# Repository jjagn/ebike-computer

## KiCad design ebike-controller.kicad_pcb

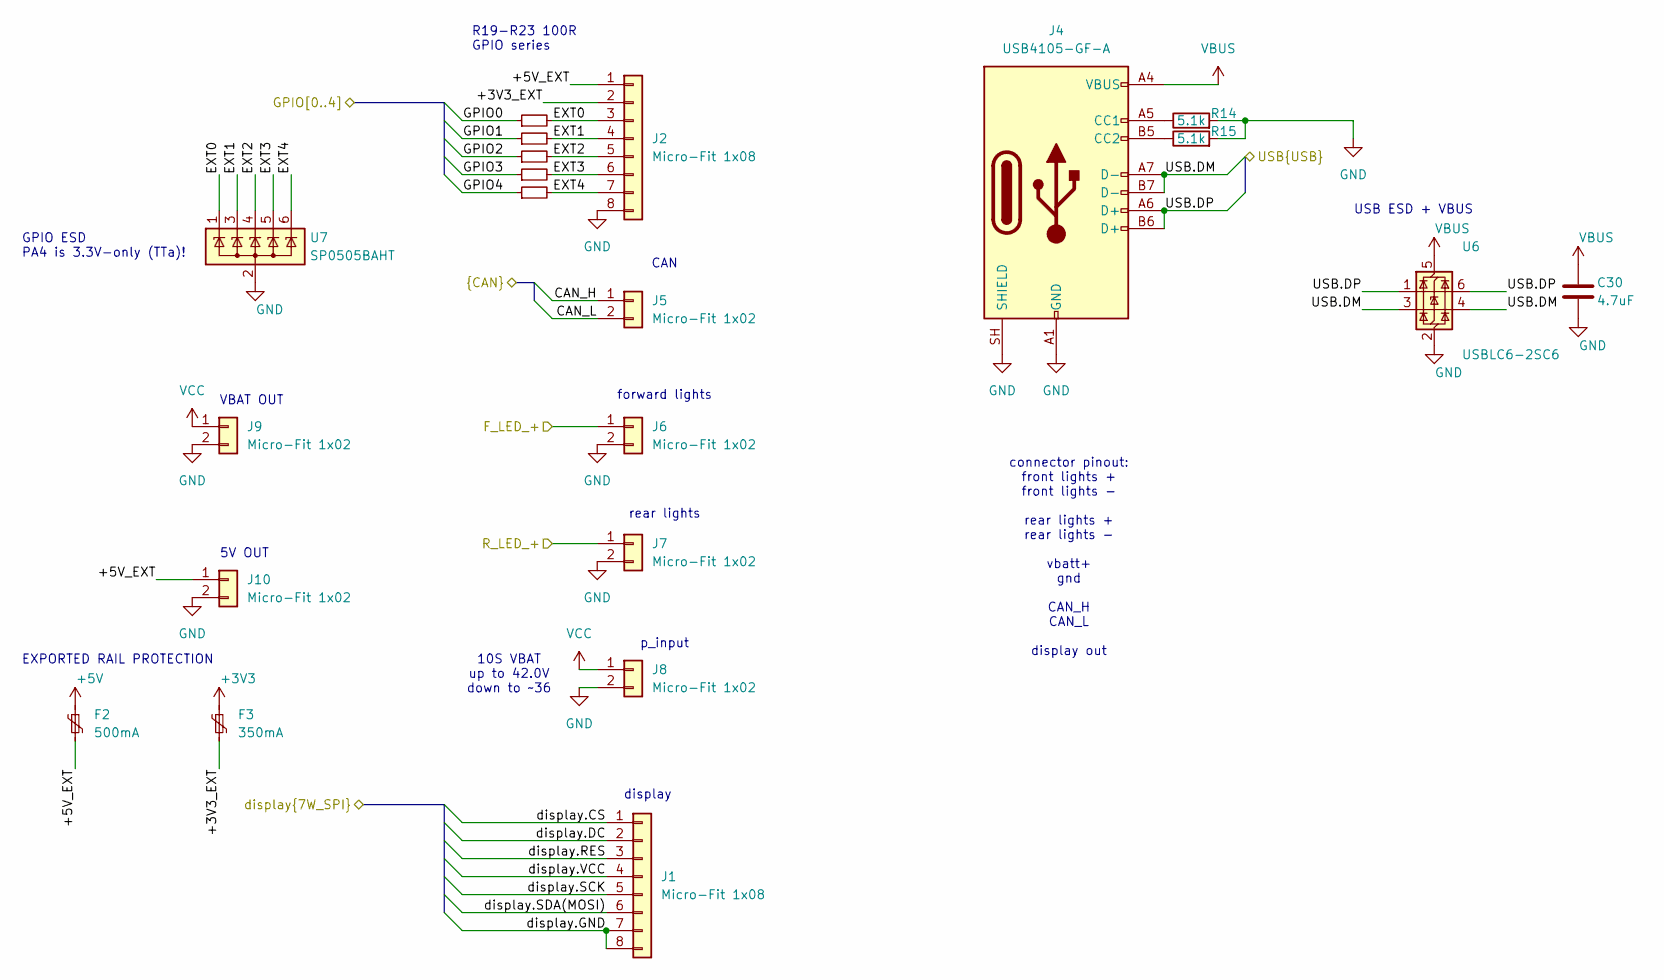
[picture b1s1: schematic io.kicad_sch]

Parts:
C30: 4.7uF; C_0603_1608Metric; Manufacturer Part Number CL10A475KO8NNNC; LCSC Part Number C19666
F2: 500mA; Fuse_0805_2012Metric; Manufacturer Part Number SMD0805B050TF; LCSC Part Number C269104
F3: 350mA; Fuse_0805_2012Metric; Manufacturer Part Number BSMD0805-035-6V; LCSC Part Number C883106
J1, J2: Micro-Fit 1x08; Molex_Micro-Fit_3.0_43650-0800_1x08_P3.00mm_Horizontal; Manufacturer Part Number 0436500800
J4: USB4105-GF-A; USB_C_Receptacle_GCT_USB4105-xx-A_16P_TopMnt_Horizontal; Manufacturer Part Number USB4105-GF-A; LCSC Part Number C3020560
J5, J6, J7, J8, J9, J10: Micro-Fit 1x02; Molex_Micro-Fit_3.0_43650-0200_1x02_P3.00mm_Horizontal; Manufacturer Part Number 0436500200
R14, R15: 5.1k; R_0402_1005Metric; Manufacturer Part Number 0402WGF5101TCE; LCSC Part Number C25905
R19, R20, R21, R22, R23: 100R; R_0402_1005Metric; Manufacturer Part Number 0402WGF1000TCE; LCSC Part Number C25076
U6: USBLC6-2SC6; SOT-23-6; Manufacturer Part Number USBLC6-2SC6; LCSC Part Number C7519
U7: SP0505BAHT; SOT-23-6; Manufacturer Part Number SP0505BAHTG; LCSC Part Number C151299

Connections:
+3V3: F3.1, J1.4; also elsewhere on the board
+5V: F2.1; also elsewhere on the board
/IO/+3V3_EXT: F3.2, J2.2
/IO/+5V_EXT: F2.2, J2.1, J10.1
/IO/CAN_H: J5.1; also elsewhere on the board
/IO/CAN_L: J5.2; also elsewhere on the board
/IO/EXT0: J2.3, R19.2, U7.1 (K)
/IO/EXT1: J2.4, R20.2, U7.3 (K)
/IO/EXT2: J2.5, R21.2, U7.4 (K)
/IO/EXT3: J2.6, R22.2, U7.5 (K)
/IO/EXT4: J2.7, R23.2, U7.6 (K)
/IO/F_LED_+: J6.1
/IO/GPIO0: R19.1; also elsewhere on the board
/IO/GPIO1: R20.1; also elsewhere on the board
/IO/GPIO2: R21.1; also elsewhere on the board
/IO/GPIO3: R22.1; also elsewhere on the board
/IO/GPIO4: R23.1; also elsewhere on the board
/IO/R_LED_+: J7.1
/IO/USB.DM: J4.A7 (D-), J4.B7 (D-), U6.3 (I/O2), U6.4 (I/O2); also elsewhere on the board
/IO/USB.DP: J4.A6 (D+), J4.B6 (D+), U6.1 (I/O1), U6.6 (I/O1); also elsewhere on the board
/IO/display.CS: J1.1; also elsewhere on the board
/IO/display.DC: J1.2; also elsewhere on the board
/IO/display.RES: J1.3; also elsewhere on the board
/IO/display.SCK: J1.5; also elsewhere on the board
/IO/display.SDA(MOSI): J1.6; also elsewhere on the board
GND: C30.2, J1.7, J1.8, J2.8, J4.A1 (GND), J4.A12 (GND), J4.B1 (GND), J4.B12 (GND), J4.SH (SHIELD), J6.2, J7.2, J8.2, J9.2, J10.2, R14.2, R15.2, U6.2 (GND), U7.2 (A); also elsewhere on the board
unnamed: J4.A5 (CC1), R14.1
unnamed: J4.B5 (CC2), R15.1
VBUS: C30.1, J4.A4 (VBUS), J4.A9 (VBUS), J4.B4 (VBUS), J4.B9 (VBUS), U6.5 (VBUS); also elsewhere on the board
VCC: J8.1, J9.1; also elsewhere on the board

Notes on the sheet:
connector pinout: front lights + front lights - rear lights + rear lights - vbatt+ gnd CAN_H CAN_L display out
5V OUT
CAN
p_input
VBAT OUT
10S VBAT up to 42.0V down to ~36
forward lights
display
rear lights
USB ESD + VBUS
R19-R23 100R GPIO series
GPIO ESD PA4 is 3.3V-only (TTa)!
EXPORTED RAIL PROTECTION

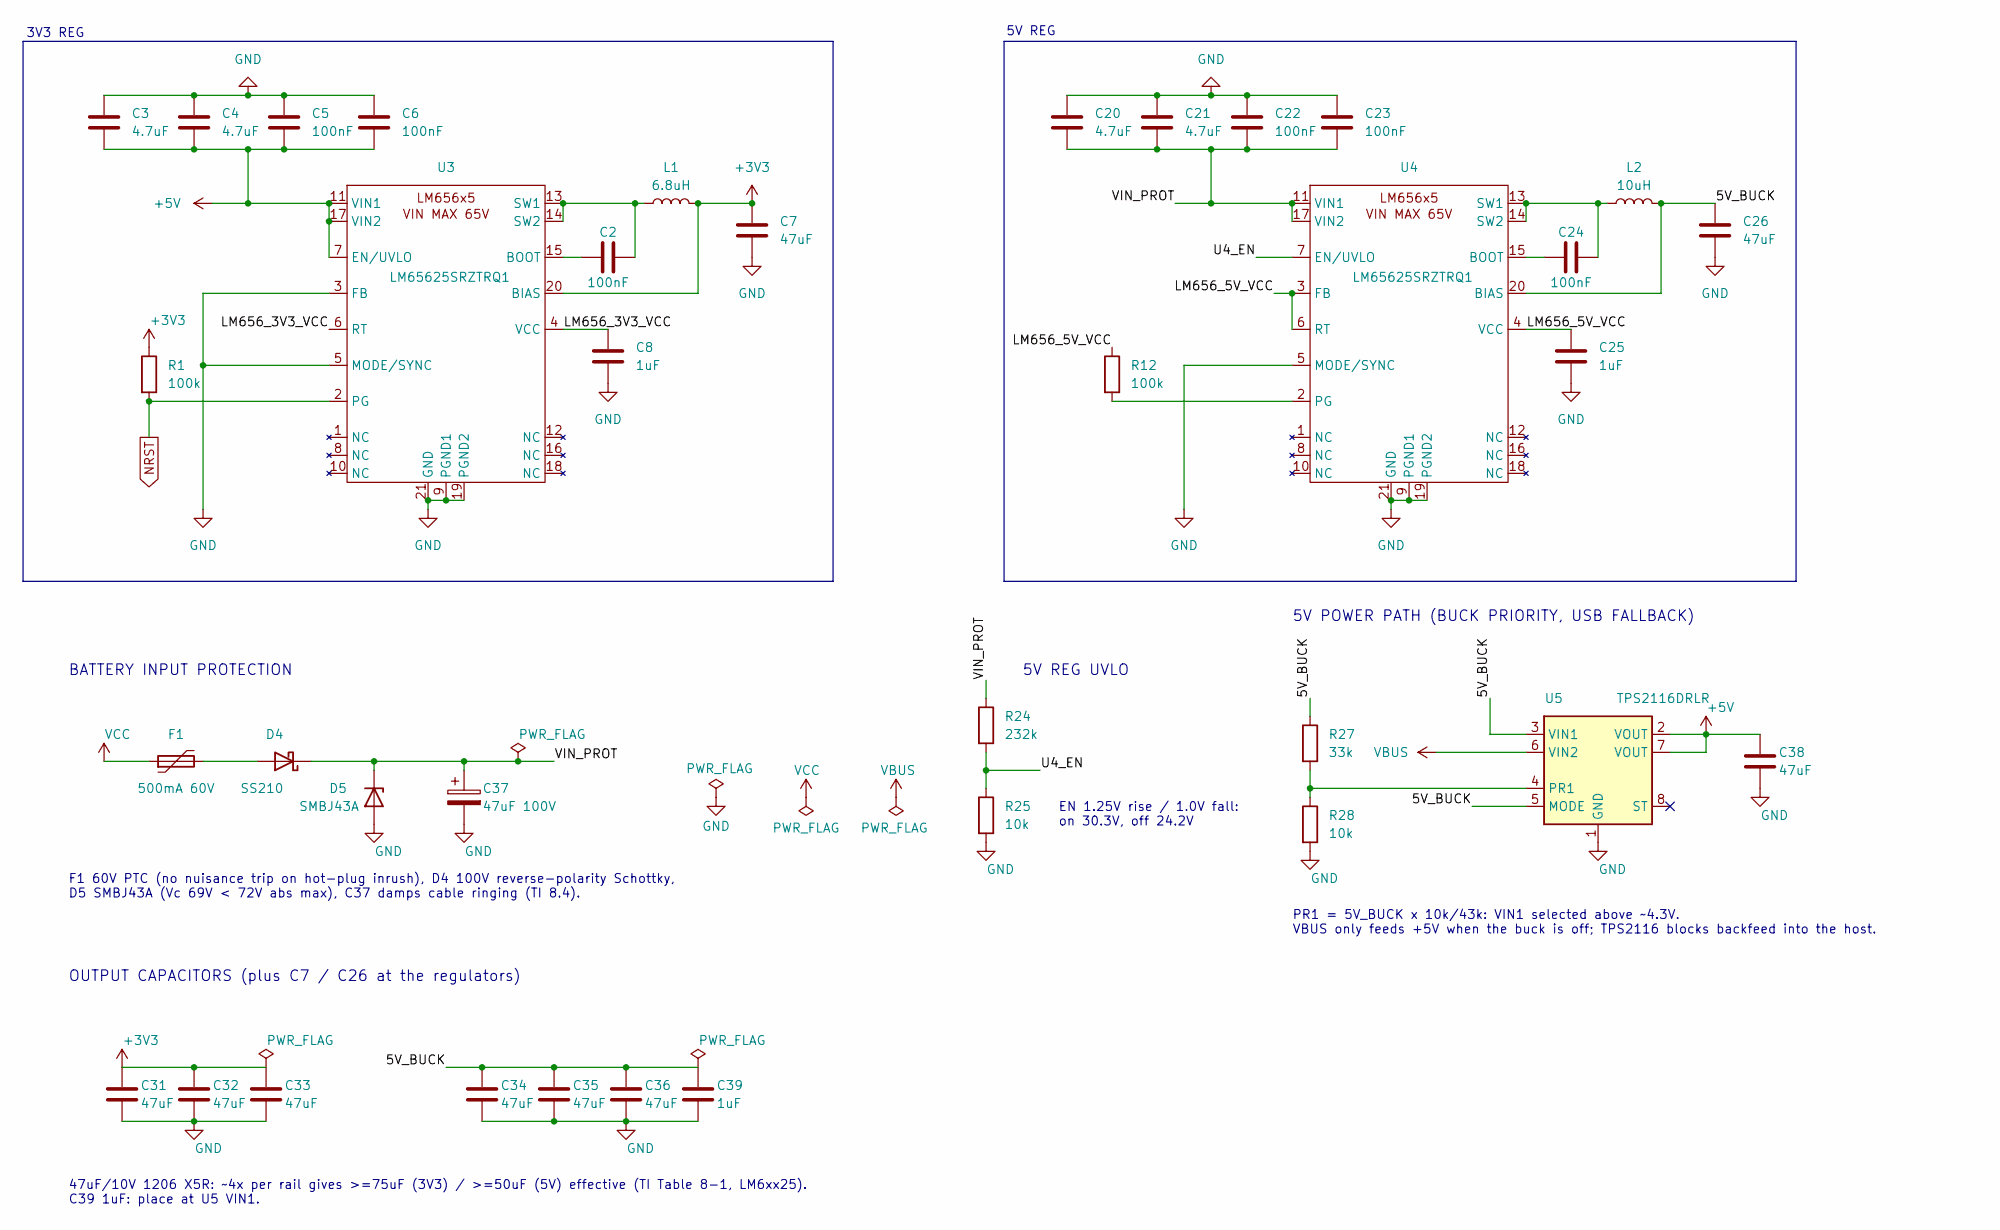
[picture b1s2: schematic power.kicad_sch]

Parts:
C2, C5, C6, C24: 100nF; C_0402_1005Metric; Manufacturer Part Number CL05B104KB54PNC; LCSC Part Number C307331
C3, C4: 4.7uF; C_0805_2012Metric; Manufacturer Part Number CL21A475KAQNNNE; LCSC Part Number C1779
C7, C26, C31, C32, C33, C34, C35, C36, C38: 47uF; C_1206_3216Metric; Manufacturer Part Number CL31A476MPHNNNE; LCSC Part Number C96123
C8, C25, C39: 1uF; C_0402_1005Metric; Manufacturer Part Number CL05A105KA5NQNC; LCSC Part Number C52923
C20, C21: 4.7uF; C_1210_3225Metric; Manufacturer Part Number CL32Y475KCIVPNE; LCSC Part Number C2803397
C22, C23: 100nF; C_0603_1608Metric; Manufacturer Part Number CL10B104KC8NNNC; LCSC Part Number C15725
C37: 47uF 100V; CP_Elec_10x10; Manufacturer Part Number VEJ470M2ATR-1010; LCSC Part Number C134777
D4: SS210; D_SMA; Manufacturer Part Number SS210; LCSC Part Number C14996
D5: SMBJ43A; D_SMB; Manufacturer Part Number SMBJ43A; LCSC Part Number C5353274
F1: 500mA 60V; Fuse_1812_4532Metric; Manufacturer Part Number mSMD050-60V; LCSC Part Number C70113
L1: 6.8uH; Inductor_SMD_7.4mmx6.6mm; Manufacturer Part Number GSM0630-6R8-M; LCSC Part Number C51933839
L2: 10uH; Inductor_SMD_7.4mmx6.6mm; Manufacturer Part Number SRG0630-100-M; LCSC Part Number C53462991
R1, R12: 100k; R_0402_1005Metric; Manufacturer Part Number 0402WGF1003TCE; LCSC Part Number C25741
R24: 232k; R_0402_1005Metric; Manufacturer Part Number FRC0402F2323TS; LCSC Part Number C3013159
R25, R28: 10k; R_0402_1005Metric; Manufacturer Part Number 0402WGF1002TCE; LCSC Part Number C25744
R27: 33k; R_0402_1005Metric; Manufacturer Part Number 0402WGF3302TCE; LCSC Part Number C25779
U3, U4: LM65625SRZTRQ1; TI_RZT0020A; Manufacturer Part Number LM65625SRZTRQ1; LCSC Part Number C49305977
U5: TPS2116DRLR; SOT-583-8; Manufacturer Part Number TPS2116DRLR; LCSC Part Number C3235557

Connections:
+3V3: C7.1, C31.1, C32.1, C33.1, L1.2, R1.1, U3.20 (BIAS); also elsewhere on the board
+5V: C3.2, C4.2, C5.2, C6.2, C38.1, U3.7 (EN/UVLO), U3.11 (VIN1), U3.17 (VIN2), U5.2 (VOUT), U5.7 (VOUT); also elsewhere on the board
/Power/5V_BUCK: C26.1, C34.1, C35.1, C36.1, C39.1, L2.2, R27.1, U4.20 (BIAS), U5.3 (VIN1), U5.5 (MODE)
/Power/LM656_3V3_VCC: C8.1, U3.4 (VCC), U3.6 (RT)
/Power/LM656_5V_VCC: C25.1, R12.1, U4.3 (FB), U4.4 (VCC), U4.6 (RT)
/Power/U4_EN: R24.2, R25.1, U4.7 (EN/UVLO)
/Power/VIN_PROT: C20.2, C21.2, C22.2, C23.2, C37.1, D4.1 (K), D5.1 (K), R24.1, U4.11 (VIN1), U4.17 (VIN2)
GND: C3.1, C4.1, C5.1, C6.1, C7.2, C8.2, C20.1, C21.1, C22.1, C23.1, C25.2, C26.2, C31.2, C32.2, C33.2, C34.2, C35.2, C36.2, C37.2, C38.2, C39.2, D5.2 (A), R25.2, R28.2, U3.3 (FB), U3.5 (MODE/SYNC), U3.9 (PGND1), U3.19 (PGND2), U3.21 (GND), U4.5 (MODE/SYNC), U4.9 (PGND1), U4.19 (PGND2), U4.21 (GND), U5.1 (GND); also elsewhere on the board
NRST: R1.2, U3.2 (PG); also elsewhere on the board
unnamed: D4.2 (A), F1.2
unnamed: C2.1, U3.15 (BOOT)
unnamed: C2.2, L1.1, U3.13 (SW1), U3.14 (SW2)
unnamed: C24.1, U4.15 (BOOT)
unnamed: R12.2, U4.2 (PG)
unnamed: C24.2, L2.1, U4.13 (SW1), U4.14 (SW2)
unnamed: R27.2, R28.1, U5.4 (PR1)
VBUS: U5.6 (VIN2); also elsewhere on the board
VCC: F1.1; also elsewhere on the board

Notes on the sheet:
PR1 = 5V_BUCK x 10k/43k: VIN1 selected above ~4.3V. VBUS only feeds +5V when the buck is off; TPS2116 blocks backfeed into the host.
5V REG
47uF/10V 1206 X5R: ~4x per rail gives >=75uF (3V3) / >=50uF (5V) effective (TI Table 8-1, LM6xx25). C39 1uF: place at U5 VIN1.
BATTERY INPUT PROTECTION
EN 1.25V rise / 1.0V fall: on 30.3V, off 24.2V
5V REG UVLO
5V POWER PATH (BUCK PRIORITY, USB FALLBACK)
OUTPUT CAPACITORS (plus C7 / C26 at the regulators)
3V3 REG
F1 60V PTC (no nuisance trip on hot-plug inrush), D4 100V reverse-polarity Schottky, D5 SMBJ43A (Vc 69V < 72V abs max), C37 damps cable ringing (TI 8.4).

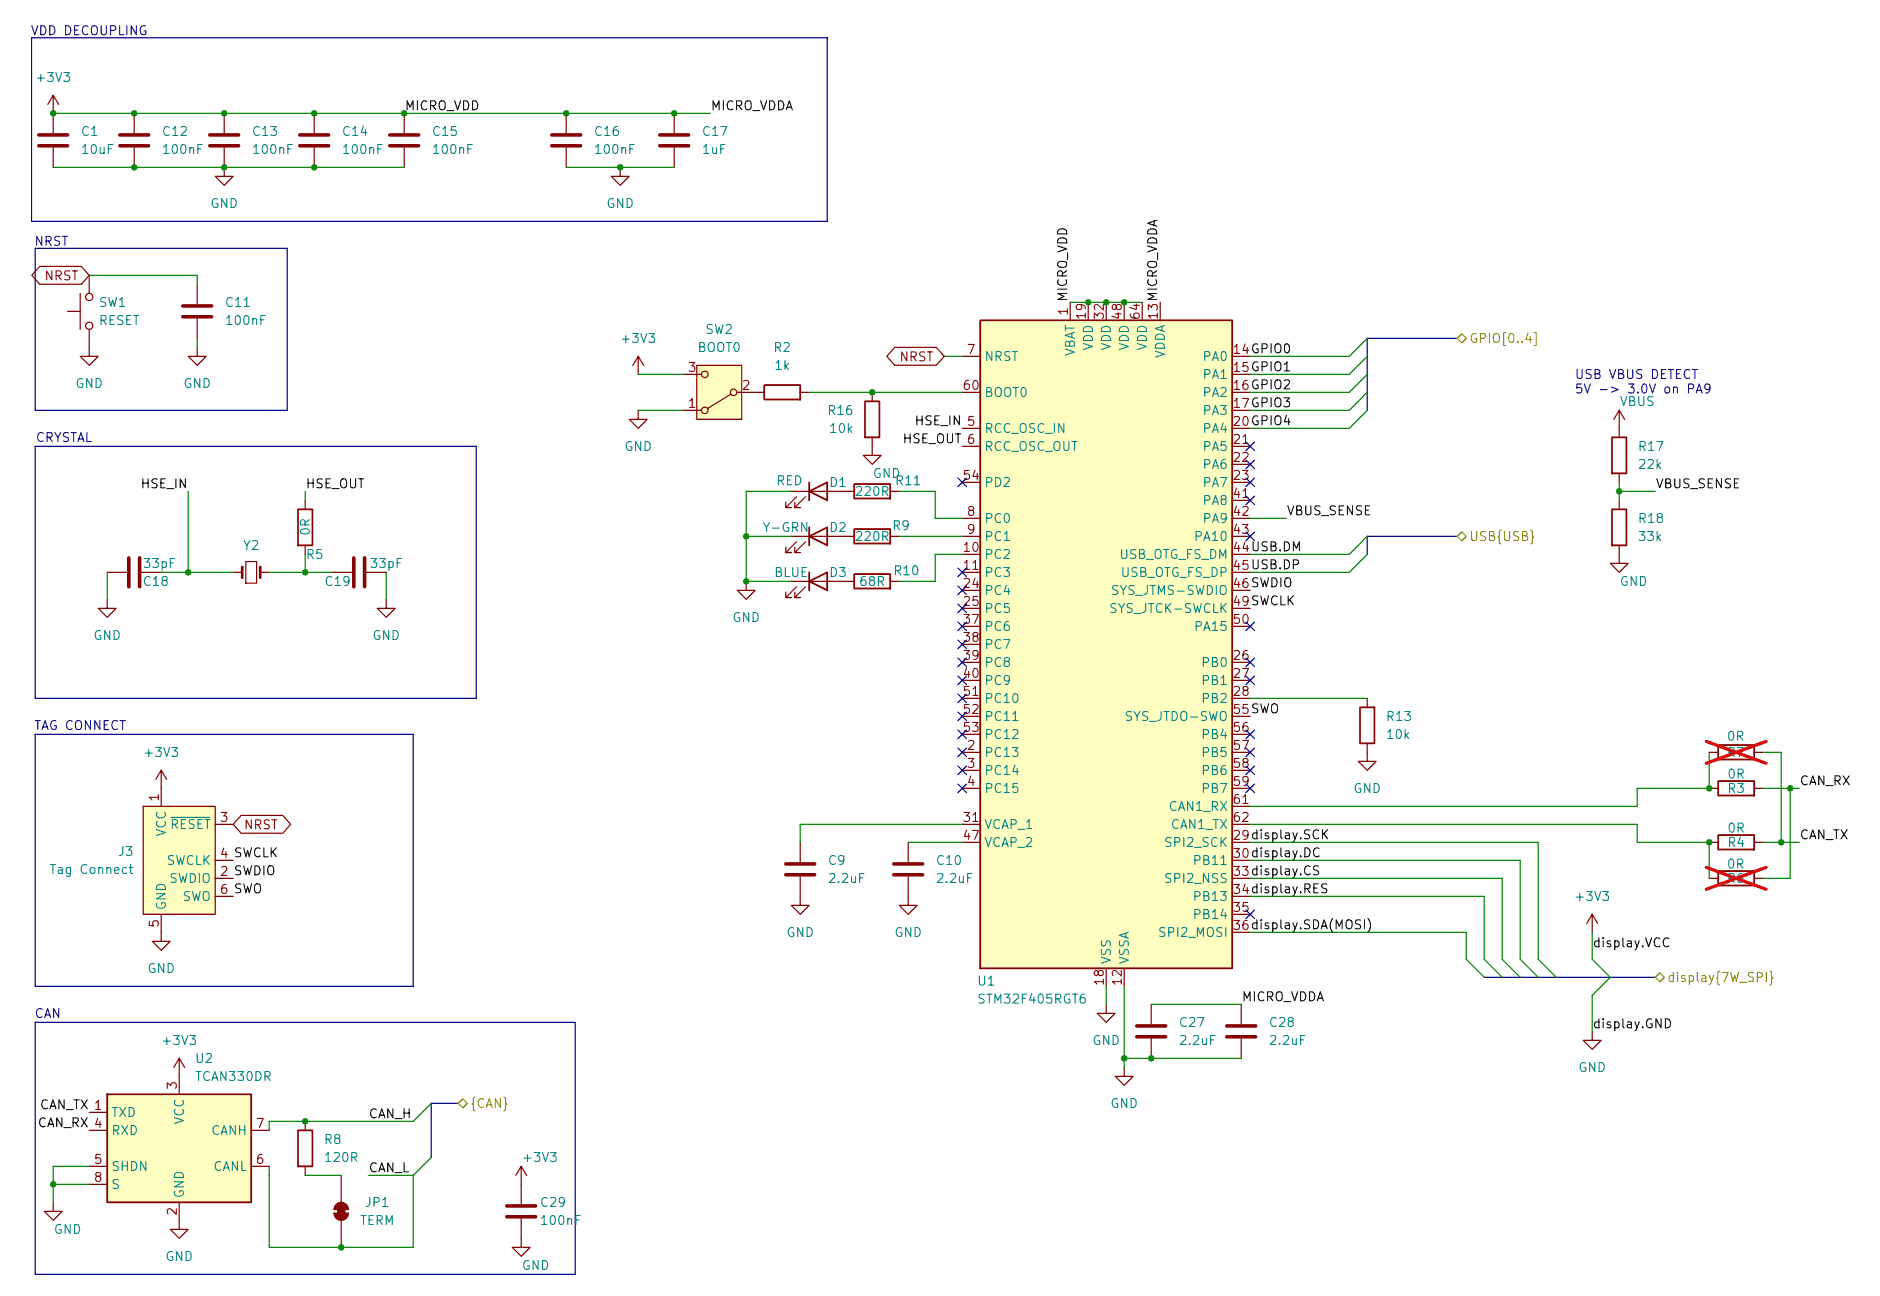
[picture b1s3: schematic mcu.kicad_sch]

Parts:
C1: 10uF; C_0805_2012Metric; Manufacturer Part Number CL21A106KAYNNNE; LCSC Part Number C15850
C9, C10, C27, C28: 2.2uF; C_0402_1005Metric; Manufacturer Part Number CL05A225MQ5NSNC; LCSC Part Number C12530
C11, C12, C13, C14, C15, C16, C29: 100nF; C_0402_1005Metric; Manufacturer Part Number CL05B104KB54PNC; LCSC Part Number C307331
C17: 1uF; C_0402_1005Metric; Manufacturer Part Number CL05A105KA5NQNC; LCSC Part Number C52923
C18, C19: 33pF; C_0402_1005Metric; Manufacturer Part Number 0402CG330J500NT; LCSC Part Number C1562
D1: RED; LED_0603_1608Metric; Manufacturer Part Number KT-0603R; LCSC Part Number C2286
D2: Y-GRN; LED_0603_1608Metric; Manufacturer Part Number KT-0603YG; LCSC Part Number C2289
D3: BLUE; LED_0603_1608Metric; Manufacturer Part Number 19-217/BHC-ZL1M2RY/6T; LCSC Part Number C2986058
J3: Tag Connect; Tag-Connect_TC2030-IDC-FP_2x03_P1.27mm_Vertical
JP1: TERM; SolderJumper-2_P1.3mm_Bridged_RoundedPad1.0x1.5mm
R2: 1k; R_0402_1005Metric; Manufacturer Part Number 0402WGF1001TCE; LCSC Part Number C11702
R3, R4, R5: 0R; R_0603_1608Metric; Manufacturer Part Number 0603WAF0000T5E; LCSC Part Number C21189
R6, R7: 0R; R_0603_1608Metric; Manufacturer Part Number 0603WAF0000T5E; LCSC Part Number C21189; not fitted
R8: 120R; R_0402_1005Metric; Manufacturer Part Number 0402WGF1200TCE; LCSC Part Number C25079
R9, R11: 220R; R_0402_1005Metric; Manufacturer Part Number 0402WGF2200TCE; LCSC Part Number C25091
R10: 68R; R_0402_1005Metric; Manufacturer Part Number FRC0402F68R0TS; LCSC Part Number C2909380
R13, R16: 10k; R_0402_1005Metric; Manufacturer Part Number 0402WGF1002TCE; LCSC Part Number C25744
R17: 22k; R_0402_1005Metric; Manufacturer Part Number 0402WGF2202TCE; LCSC Part Number C25768
R18: 33k; R_0402_1005Metric; Manufacturer Part Number 0402WGF3302TCE; LCSC Part Number C25779
SW1: RESET; SW_Push_1P1T_XKB_TS-1187A; Manufacturer Part Number TS-1187A-B-A-B; LCSC Part Number C318884
SW2: BOOT0; SW_SPDT_Shouhan_MSK12C02; Manufacturer Part Number MSK12C02; LCSC Part Number C431540
U1: STM32F405RGT6; LQFP-64_10x10mm_P0.5mm; Manufacturer Part Number STM32F405RGT6; LCSC Part Number C15742
U2: TCAN330DR; SOIC-8_3.9x4.9mm_P1.27mm; Manufacturer Part Number TCAN330DR; LCSC Part Number C2652876
Y2: 8MHz 20pF; Crystal_SMD_5032-2Pin_5.0x3.2mm; Manufacturer Part Number X50328MSB2GI; LCSC Part Number C115962

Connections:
+3V3: C1.1, C12.1, C13.1, C14.1, C15.1, C16.1, C17.1, C27.2, C28.2, C29.1, J3.1 (VCC), SW2.3 (C), U1.1 (VBAT), U1.13 (VDDA), U1.19 (VDD), U1.32 (VDD), U1.48 (VDD), U1.64 (VDD), U2.3 (VCC); also elsewhere on the board
/IO/CAN_H: R8.1, U2.7 (CANH); also elsewhere on the board
/IO/CAN_L: JP1.1 (A), U2.6 (CANL); also elsewhere on the board
/IO/GPIO0: U1.14 (PA0); also elsewhere on the board
/IO/GPIO1: U1.15 (PA1); also elsewhere on the board
/IO/GPIO2: U1.16 (PA2); also elsewhere on the board
/IO/GPIO3: U1.17 (PA3); also elsewhere on the board
/IO/GPIO4: U1.20 (PA4); also elsewhere on the board
/IO/USB.DM: U1.44 (USB_OTG_FS_DM); also elsewhere on the board
/IO/USB.DP: U1.45 (USB_OTG_FS_DP); also elsewhere on the board
/IO/display.CS: U1.33 (SPI2_NSS); also elsewhere on the board
/IO/display.DC: U1.30 (PB11); also elsewhere on the board
/IO/display.RES: U1.34 (PB13); also elsewhere on the board
/IO/display.SCK: U1.29 (SPI2_SCK); also elsewhere on the board
/IO/display.SDA(MOSI): U1.36 (SPI2_MOSI); also elsewhere on the board
/MCU/CAN_RX: R3.2, R6.1, U2.4 (RXD)
/MCU/CAN_TX: R4.2, R7.1, U2.1 (TXD)
/MCU/HSE_IN: C18.2, U1.5 (RCC_OSC_IN), Y2.1
/MCU/HSE_OUT: R5.1, U1.6 (RCC_OSC_OUT)
/MCU/SWCLK: J3.4 (SWCLK), U1.49 (SYS_JTCK-SWCLK)
/MCU/SWDIO: J3.2 (SWDIO), U1.46 (SYS_JTMS-SWDIO)
/MCU/SWO: J3.6 (SWO), U1.55 (SYS_JTDO-SWO)
/MCU/VBUS_SENSE: R17.2, R18.1, U1.42 (PA9)
GND: C1.2, C9.1, C10.1, C11.2, C12.2, C13.2, C14.2, C15.2, C16.2, C17.2, C18.1, C19.2, C27.1, C28.1, C29.2, D1.1 (K), D2.1 (K), D3.1 (K), J3.5 (GND), R13.1, R16.2, R18.2, SW1.1, SW2.1 (A), U1.12 (VSSA), U1.18 (VSS), U1.63 (VSS), U2.2 (GND), U2.5 (SHDN), U2.8 (S); also elsewhere on the board
NRST: C11.1, J3.3 (~RESET), SW1.2, U1.7 (NRST); also elsewhere on the board
unnamed: C19.1, R5.2, Y2.2
unnamed: D1.2 (A), R11.1
unnamed: D2.2 (A), R9.1
unnamed: D3.2 (A), R10.1
unnamed: JP1.2 (B), R8.2
unnamed: R2.1, SW2.2 (B)
unnamed: R2.2, R16.1, U1.60 (BOOT0)
unnamed: R13.2, U1.28 (PB2)
unnamed: R3.1, R7.2, U1.61 (CAN1_RX)
unnamed: R4.1, R6.2, U1.62 (CAN1_TX)
unnamed: R11.2, U1.8 (PC0)
unnamed: R9.2, U1.9 (PC1)
unnamed: R10.2, U1.10 (PC2)
unnamed: C9.2, U1.31 (VCAP_1)
unnamed: C10.2, U1.47 (VCAP_2)
VBUS: R17.1; also elsewhere on the board

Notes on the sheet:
CAN
VDD DECOUPLING
NRST
CRYSTAL
TAG CONNECT
USB VBUS DETECT 5V -> 3.0V on PA9

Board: 2 copper layers, 97 parts (0 on the bottom side), 64 nets, no tracks yet.
